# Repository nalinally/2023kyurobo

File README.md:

# 本名刺基板の使い方

本基板名刺は、Arduinoにプログラムを書き込んで挿すことで、連打綱引きゲームができるようになります。<br>
※動作確認はしておりません。あしからず。

## １．部品の実装
### 用意するもの
・[タクトスイッチ](https://akizukidenshi.com/catalog/g/gP-03647/)  2個 <br>
・[led](https://akizukidenshi.com/catalog/g/gI-11577/)  7個<br>
・[1ｋくらいの抵抗](https://akizukidenshi.com/catalog/g/gR-25102/)  7本<br>

基板に書いてある通りに実装していきます

## ２．Arduinoへプログラム書き込み

Arduino IDE を使って、同リポジトリ内の2023kyurobo.cをArduinoに書き込みます<br>
※プログラムは、Arduino UNO R3 での動作を想定して書かれています

## ３．遊ぶ

### スタート方法

両者がスイッチを押すとカウントが始まり、その状態で3秒間押し続けて、真ん中のLEDが光るとゲームスタートです

### ゲーム中

ひたすらスイッチを連打します。最初は真ん中のLEDが光っていますが、より連打数が多いほうに徐々に引き寄せられていきます。

### ゲームの勝敗

自分に一番近いLEDを先に光らせたほうの勝利です。

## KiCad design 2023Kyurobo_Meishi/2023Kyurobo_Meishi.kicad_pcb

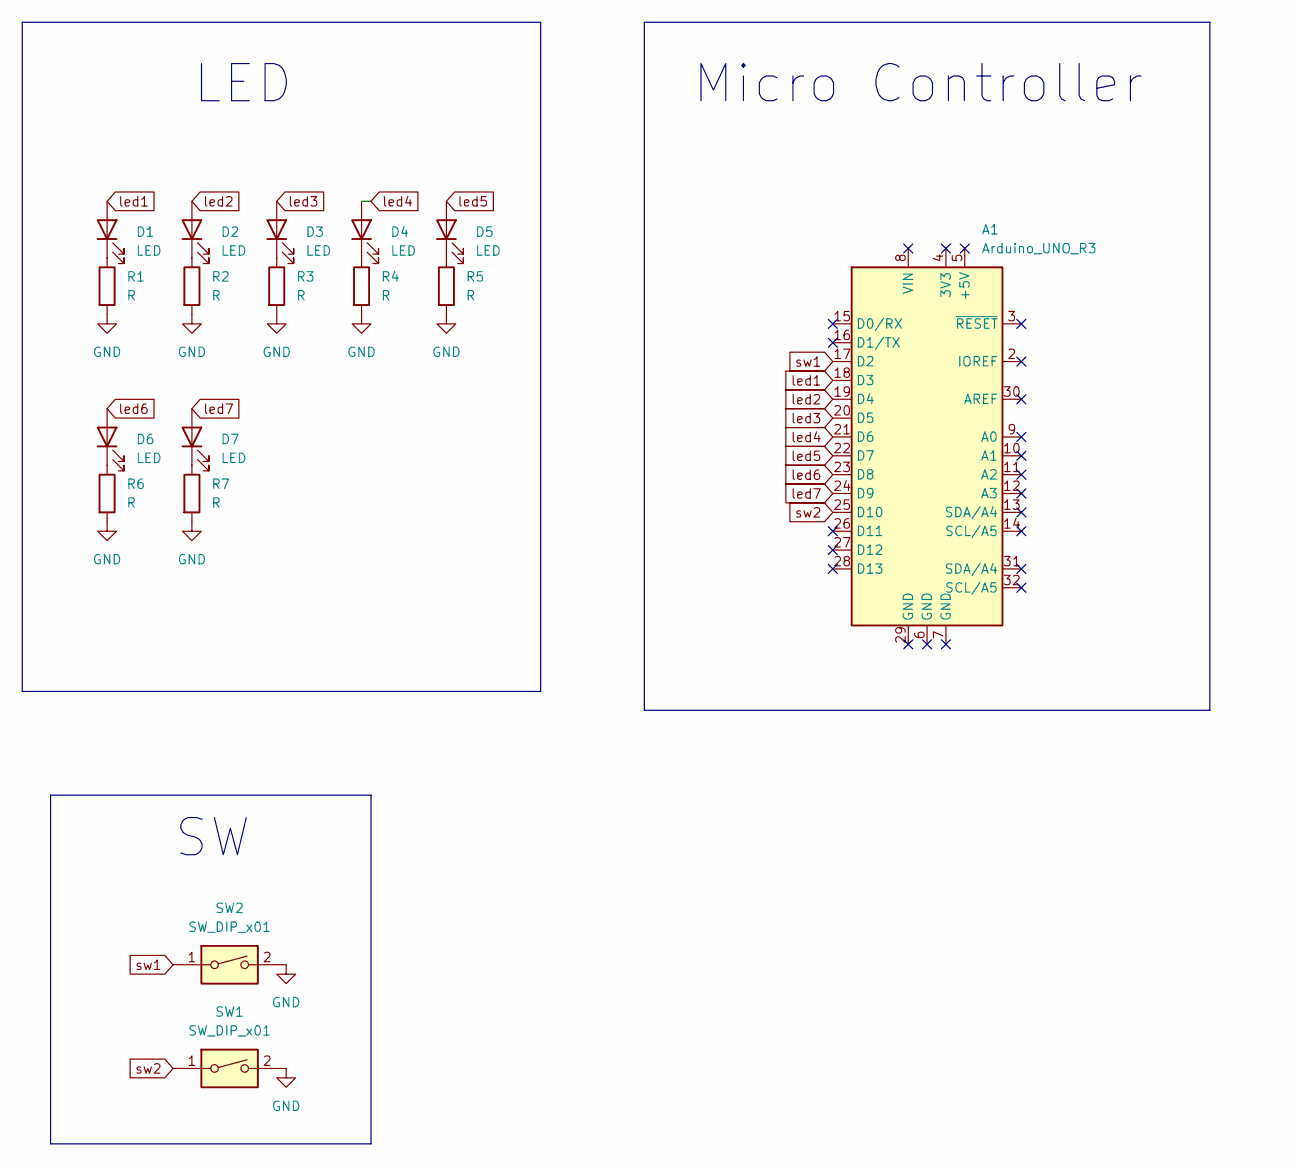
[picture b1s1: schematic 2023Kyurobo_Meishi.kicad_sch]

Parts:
A1: Arduino_UNO_R3
D1, D2, D3, D4, D5, D6, D7: LED; LED_D3.0mm
R1, R2, R3, R4, R5, R6, R7: R; R_Axial_DIN0204_L3.6mm_D1.6mm_P7.62mm_Horizontal
SW1, SW2: SW_DIP_x01; SW_PUSH_6mm_H7.3mm

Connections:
GND: R1.2, R2.2, R3.2, R4.2, R5.2, R6.2, R7.2, SW1.2, SW2.2
unnamed: D1.1 (K), R1.1
unnamed: D2.1 (K), R2.1
unnamed: D3.1 (K), R3.1
unnamed: D4.1 (K), R4.1
unnamed: D5.1 (K), R5.1
unnamed: D6.1 (K), R6.1
unnamed: D7.1 (K), R7.1
led1: A1.18 (D3), D1.2 (A)
led2: A1.19 (D4), D2.2 (A)
led3: A1.20 (D5), D3.2 (A)
led4: A1.21 (D6), D4.2 (A)
led5: A1.22 (D7), D5.2 (A)
led6: A1.23 (D8), D6.2 (A)
led7: A1.24 (D9), D7.2 (A)
sw1: A1.17 (D2), SW2.1
sw2: A1.25 (D10), SW1.1

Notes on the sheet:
LED
Micro Controller

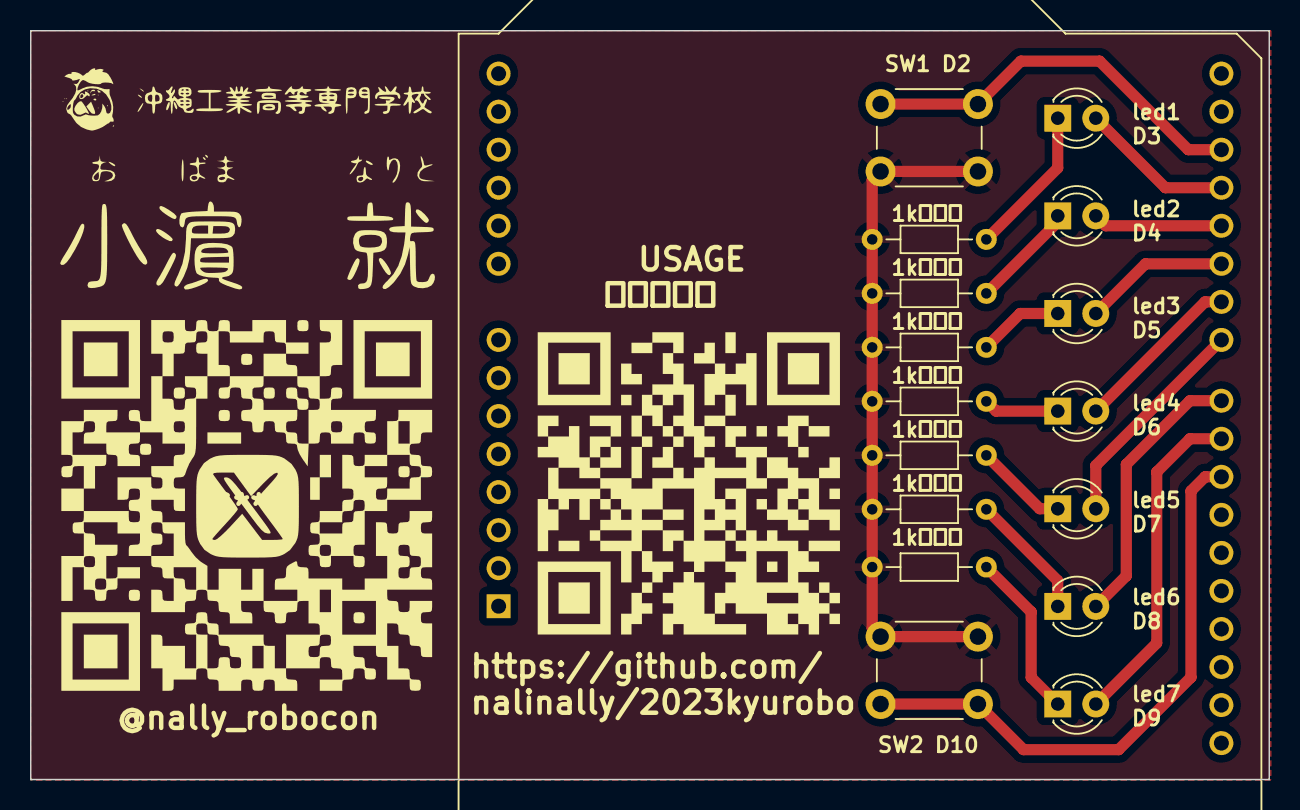
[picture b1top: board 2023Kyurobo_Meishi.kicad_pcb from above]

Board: 2 copper layers, 82.7 x 50.0 mm, 17 parts (0 on the bottom side), 17 nets.

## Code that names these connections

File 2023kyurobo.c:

#define sw1 D2
#define led1 D3
#define led2 D4
#define led3 D5
#define led4 D6
#define led5 D7
#define led6 D8
#define led7 D9
#define sw2 D10
#define step 5

int sw1_val_pre = 0, sw2_val_pre = 0;
int sw1_val = 0, sw2_val = 0;
int count = 0;
int phase = 0;  // 0 ... スタート前 

void setup() {
  pinMode(sw1, INPUT_PULLUP);
  pinMode(sw2, INPUT_PULLUP);
  Serial.begin(9600);
}

void loop() {

  sw1_val_pre = sw1_val;
  sw2_val_pre = sw2_val;
  sw1_val = !digitalRead(sw1);
  sw2_val = !digitalRead(sw2);

  switch(phase){

    case 0:
      if(sw1_val && sw2_val){
        count++;
      }
      else{
        count = 0;
      }
      if(count = 0){
        setled(LOW, LOW, LOW, LOW, LOW, LOW, LOW);
      }
      if(count > 0 && count < 100){
        setled(HIGH, LOW, LOW, LOW, LOW, LOW, HIGH);
      }
      if(count >= 100 && count < 200){
        setled(LOW, HIGH, LOW, LOW, LOW, HIGH, LOW);
      }
      if(count >= 200 && count < 300){
        setled(LOW, LOW, HIGH, LOW, HIGH, LOW, LOW);
      }
      if(count >= 300){
        setled(LOW, LOW, LOW, HIGH, LOW, LOW, LOW);
        count = step * 3;
        phase = 1;
      }
      delay(10);
      break;

    case 1:
      if(!sw1_val_pre && sw1_val){
        count++;
      }
      if(!sw2_val_pre && sw2_val){
        count--;
      }
      if(count <= 0){
        setled(LOW, LOW, LOW, LOW, LOW, LOW, HIGH);
        phase = 2;
      }
      if(count > 0 && count <= step){
        setled(LOW, LOW, LOW, LOW, LOW, HIGH, LOW);
      }
      if(count > step && count <= step*2){
        setled(LOW, LOW, LOW, LOW, HIGH, LOW, LOW);
      }
      if(count > step*2 && count < step*4){
        setled(LOW, LOW, LOW, HIGH, LOW, LOW, LOW);
      }
      if(count >= step*4 && count < step*5){
        setled(LOW, LOW, HIGH, LOW, LOW, LOW, LOW);
      }
      if(count >= step*5 && count < step*6){
        setled(LOW, HIGH, LOW, LOW, LOW, LOW, LOW);
      }
      if(count >= step*6){
        setled(HIGH, LOW, LOW, LOW, LOW, LOW, LOW);
        phase = 2;
      }
      break;

    case 2:
      delay(3000);
      for(int i = 0; i < 3; i++){
        setled(LOW, LOW, LOW, LOW, LOW, LOW, LOW);
        delay(500);
        if(count <= 0){
          setled(LOW, LOW, LOW, LOW, LOW, LOW, HIGH);
        }
        if(count >= step*6){
          setled(HIGH, LOW, LOW, LOW, LOW, LOW, LOW);
        }
        delay(500);
      }
      delay(1000);
      setled(LOW, LOW, LOW, LOW, LOW, LOW, LOW);
      delay(1000);
      count = 0;
      phase = 0;
      break;

  }
}

void setled(int l1, int l2, int l3, int l4, int l5, int l6, int l7) {
  digitalWrite(led1, l1);
  digitalWrite(led2, l2);
  digitalWrite(led3, l3);
  digitalWrite(led4, l4);
  digitalWrite(led5, l5);
  digitalWrite(led6, l6);
  digitalWrite(led7, l7);
}
